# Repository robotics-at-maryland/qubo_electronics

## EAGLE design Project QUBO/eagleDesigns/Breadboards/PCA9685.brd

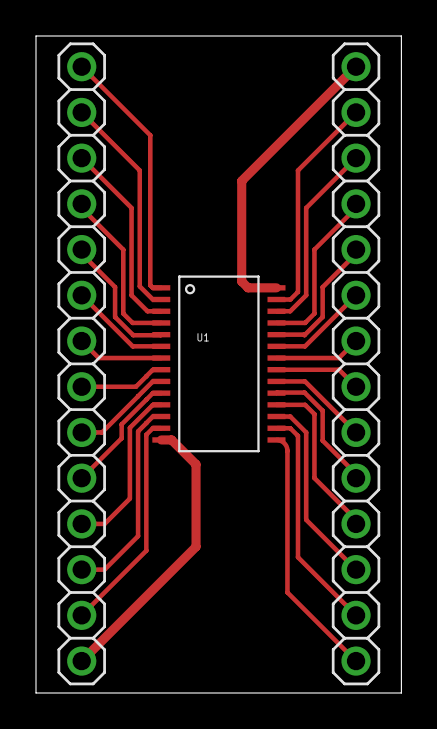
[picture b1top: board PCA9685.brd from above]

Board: 2 copper layers, 20.3 x 36.5 mm, 3 parts (0 on the bottom side), 28 nets.

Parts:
JP1, JP2: 1X14_ROUND
U1: PCA9685; TSSOP-28_4MM

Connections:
unnamed: JP1.1, U1.1
unnamed: JP1.2, U1.2
unnamed: JP1.3, U1.3
unnamed: JP1.4, U1.4
unnamed: JP1.5, U1.5
unnamed: JP1.6, U1.6
unnamed: JP1.7, U1.7
unnamed: JP1.8, U1.8
unnamed: JP1.9, U1.9
unnamed: JP1.10, U1.10
unnamed: JP1.11, U1.11
unnamed: JP1.12, U1.12
unnamed: JP1.13, U1.13
unnamed: JP1.14, U1.14
unnamed: JP2.1, U1.28
unnamed: JP2.2, U1.27
unnamed: JP2.3, U1.26
unnamed: JP2.4, U1.25
unnamed: JP2.5, U1.24
unnamed: JP2.6, U1.23
unnamed: JP2.7, U1.22
unnamed: JP2.8, U1.21
unnamed: JP2.9, U1.20
unnamed: JP2.10, U1.19
unnamed: JP2.11, U1.18
unnamed: JP2.12, U1.17
unnamed: JP2.13, U1.16
unnamed: JP2.14, U1.15

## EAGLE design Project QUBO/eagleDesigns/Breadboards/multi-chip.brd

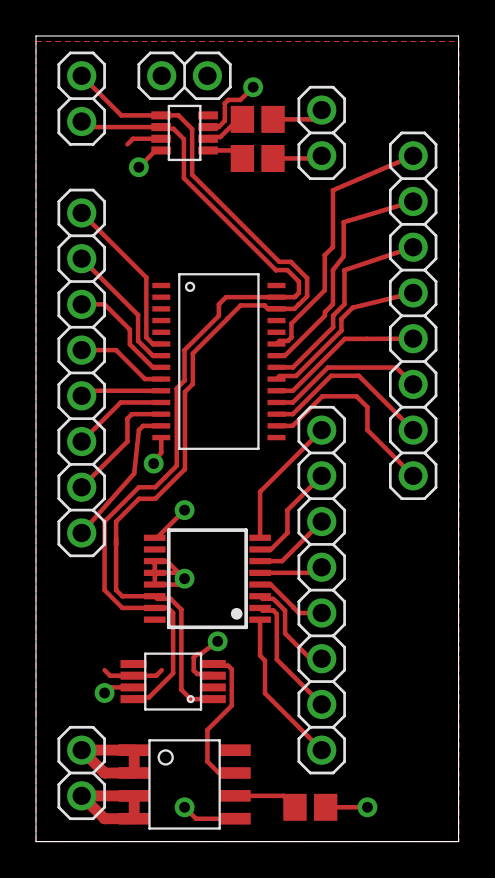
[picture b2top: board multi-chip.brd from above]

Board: 2 copper layers, 23.5 x 44.8 mm, 15 parts (0 on the bottom side), 36 nets.

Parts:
C1: 47n; C0805
I2C: 1X02
JP3, JP4: 1X02
JP5, JP8, JP9: 1X08
POWER: 1X02
R1, R2: 10; R0805
U1: PCA9685; TSSOP-28_4MM
U$1: ACS713SOIC; ACS713-SOIC
U$2: ADC121C021; VSSOP-8
U$3: ADS7828; TSSOP16
U$4: INA219SOT23; SOT-23-8

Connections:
5V: POWER.1, U1.1, U1.2, U1.3, U1.4, U1.5, U1.24, U1.28, U$1.P$8, U$2.P$5, U$2.P$6, U$3.10, U$3.16, U$4.P$4, U$4.P$7
GND: C1.2, POWER.2, U1.14, U$1.P$5, U$2.P$3, U$2.P$7, U$3.9, U$3.11, U$3.12, U$3.13, U$4.P$3, U$4.P$8
IN+: JP3.1, R1.1
IN-: JP3.2, R2.1
unnamed: C1.1, U$1.P$6
unnamed: R1.2, U$4.P$1
unnamed: R2.2, U$4.P$2
unnamed: JP4.1, U$1.P$1, U$1.P$2
unnamed: JP4.2, U$1.P$3, U$1.P$4
unnamed: U$1.P$7, U$2.P$4
unnamed: JP5.1, U$3.1
unnamed: JP5.2, U$3.2
unnamed: JP5.3, U$3.3
unnamed: JP5.4, U$3.4
unnamed: JP5.5, U$3.5
unnamed: JP5.6, U$3.6
unnamed: JP5.7, U$3.7
unnamed: JP5.8, U$3.8
unnamed: JP8.1, U1.6
unnamed: JP8.2, U1.7
unnamed: JP8.3, U1.8
unnamed: JP8.4, U1.9
unnamed: JP8.5, U1.10
unnamed: JP8.6, U1.11
unnamed: JP8.7, U1.12
unnamed: JP8.8, U1.13
unnamed: JP9.1, U1.23
unnamed: JP9.2, U1.22
unnamed: JP9.3, U1.21
unnamed: JP9.4, U1.20
unnamed: JP9.5, U1.19
unnamed: JP9.6, U1.18
unnamed: JP9.7, U1.17
unnamed: JP9.8, U1.16
SCL: I2C.2, U1.26, U$2.P$1, U$3.14, U$4.P$5
SDA: I2C.1, U1.27, U$2.P$8, U$3.15, U$4.P$6

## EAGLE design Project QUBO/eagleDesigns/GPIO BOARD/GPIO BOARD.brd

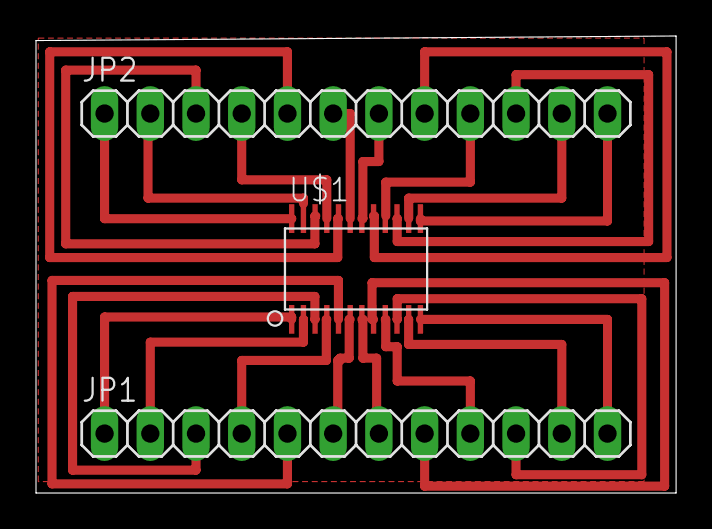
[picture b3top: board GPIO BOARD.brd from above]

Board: 2 copper layers, 35.6 x 25.4 mm, 3 parts (0 on the bottom side), 24 nets.

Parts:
JP1, JP2: 1X12
U$1: PCF8575C

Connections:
A0: JP2.4, U$1.21
A1: JP1.2, U$1.2
A2: JP1.3, U$1.3
GND: JP1.12, U$1.12
INT: JP1.1, U$1.1
P00: JP1.4, U$1.4
P01: JP1.5, U$1.5
P02: JP1.6, U$1.6
P03: JP1.7, U$1.7
P04: JP1.8, U$1.8
P05: JP1.9, U$1.9
P06: JP1.10, U$1.10
P07: JP1.11, U$1.11
P10: JP2.12, U$1.13
P11: JP2.11, U$1.14
P12: JP2.10, U$1.15
P13: JP2.9, U$1.16
P14: JP2.8, U$1.17
P15: JP2.7, U$1.18
P16: JP2.6, U$1.19
P17: JP2.5, U$1.20
SCL: JP2.3, U$1.22
SDA: JP2.2, U$1.23
VCC: JP2.1, U$1.24

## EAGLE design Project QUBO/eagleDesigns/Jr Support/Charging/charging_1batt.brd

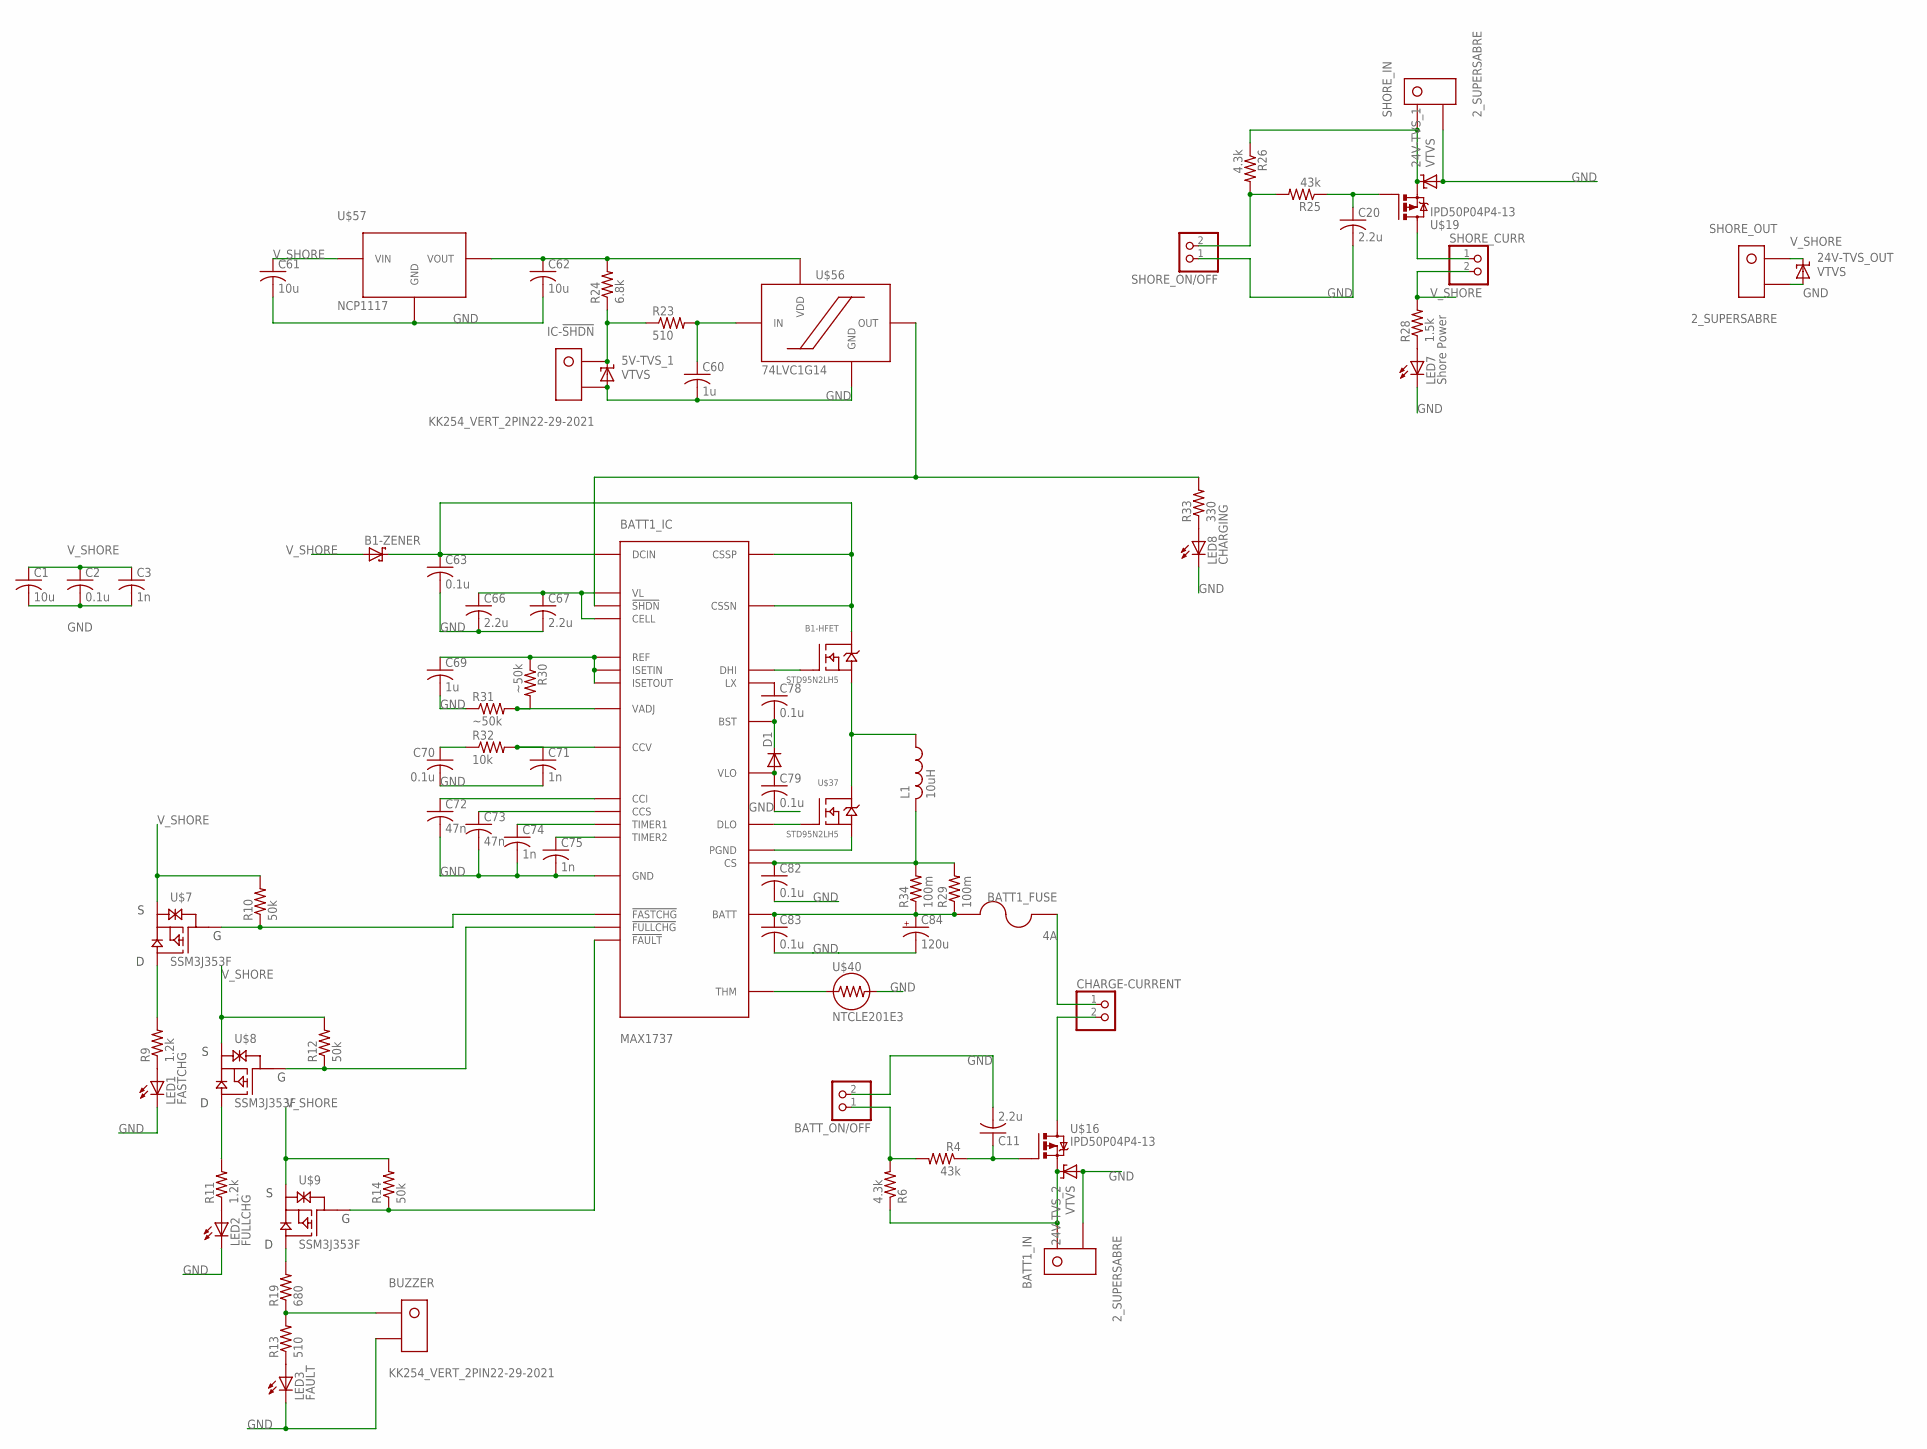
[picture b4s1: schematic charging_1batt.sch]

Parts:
5V-TVS_1, 24V-TVS_1, 24V-TVS_2, 24V-TVS_OUT: VTVS; DO-219AB
B1-HFET: STD95N2LH5; DPAK
B1-ZENER: SCHOTTKY-DIODESOD-106; SOD106-R
BATT1_FUSE: 4A; 154-OMNI-BLOK
BATT1_IC: MAX1737; QSOP28
BATT1_IN: 2_SUPERSABRE; SUPERSABRE_2CIRCUIT
BATT_ON/OFF: PINHD-1X2; 1X02
BUZZER: KK254_VERT_2PIN22-29-2021; KK254_VERT_2PIN
C1, C61, C62: 10u; C0805
C2, C63, C70, C78, C79, C82, C83: 0.1u; C0805
C3, C71, C74, C75: 1n; C0805
C11, C20, C66, C67: 2.2u; C0805
C60, C69: 1u; C0805
C72, C73: 47n; C0805
C84: 120u; E3,5-8
CHARGE-CURRENT: PINHD-1X2; 1X02
D1: DIODE-SOD123; SOD123
IC-!SHDN!: KK254_VERT_2PIN22-29-2021; KK254_VERT_2PIN
L1: 10uH; L6100
LED1: FASTCHG; CHIP-LED0805
LED2: FULLCHG; CHIP-LED0805
LED3: FAULT; CHIP-LED0805
LED7: Shore Power; CHIP-LED0805
LED8: CHARGING; CHIP-LED0805
R4, R25: 43k; R0805
R6, R26: 4.3k; R0805
R9, R11: 1.2k; R0805
R10, R12, R14: 50k; R0805
R13, R23: 510; R0805
R19: 680; R0805
R24: 6.8k; R0805
R28: 1.5k; R0805
R29, R34: 100m; R2512
R30, R31: ~50k; R0805
R32: 10k; R0805
R33: 330; R0805
SHORE_CURR: PINHD-1X2; 1X02
SHORE_IN: 2_SUPERSABRE; SUPERSABRE_2CIRCUIT
SHORE_ON/OFF: PINHD-1X2; 1X02
SHORE_OUT: 2_SUPERSABRE; SUPERSABRE_2CIRCUIT
U$7, U$8, U$9: SSM3J353F; SOT-346-3/S-MINI
U$16, U$19: IPD50P04P4-13; TO252-3
U$37: STD95N2LH5; DPAK
U$40: NTCLE201E3; 2-0.3MM-LEADS
U$56: 74LVC1G14; TSSOP5
U$57: NCP1117; SOT-223

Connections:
!SHDN!: BATT1_IC.18 (!SHDN!), R33.2, U$56.P$4 (OUT)
BATT1_P: 24V-TVS_2.P$2 (C), BATT1_IN.P$1, R6.1, U$16.TAB (D)
BATT_1: BATT1_FUSE.P$2, BATT1_IC.7 (BATT), C83.1, C84.+, R29.1, R34.1
CS_1: BATT1_IC.19 (CS), C82.1, L1.P$2 (2), R29.2, R34.2
FET-G_1: C11.1, R4.1, U$16.1 (G)
GND: 5V-TVS_1.P$1 (A), 24V-TVS_1.P$1 (A), 24V-TVS_2.P$1 (A), 24V-TVS_OUT.P$1 (A), BATT1_IC.6 (GND), BATT1_IN.P$2, BATT_ON/OFF.2, BUZZER.P$2, C1.2, C2.2, C3.2, C11.2, C20.2, C60.2, C61.2, C62.2, C63.2, C66.2, C67.2, C69.2, C70.2, C71.2, C72.2, C73.2, C74.2, C75.2, C79.2, C82.2, C83.2, C84.-, IC-!SHDN!.P$2, LED1.C, LED2.C, LED3.C, LED7.C, LED8.C, R31.1, SHORE_IN.P$2, SHORE_ON/OFF.1, SHORE_OUT.P$2, U$40.P$2 (2), U$56.P$3 (GND), U$57.P$1 (GND)
unnamed: CHARGE-CURRENT.2, U$16.3 (S)
unnamed: LED1.A, R9.1
unnamed: BATT1_FUSE.P$1, CHARGE-CURRENT.1
unnamed: SHORE_CURR.1, U$19.3 (S)
unnamed: LED3.A, R13.1
unnamed: LED2.A, R11.1
unnamed: R9.2, U$7.P$2 (D)
unnamed: BATT1_IC.16 (!FASTCHG!), R10.1, U$7.P$1 (G)
unnamed: R11.2, U$8.P$2 (D)
unnamed: BATT1_IC.17 (!FULLCHG!), R12.1, U$8.P$1 (G)
unnamed: BUZZER.P$1, R13.2, R19.1
unnamed: R19.2, U$9.P$2 (D)
unnamed: BATT1_IC.15 (!FAULT!), R14.1, U$9.P$1 (G)
unnamed: LED7.A, R28.1
unnamed: B1-HFET.TAB (D), B1-ZENER.C, BATT1_IC.26 (CSSN), BATT1_IC.27 (CSSP), BATT1_IC.28 (DCIN), C63.1
unnamed: C20.1, R25.1, U$19.1 (G)
unnamed: C60.1, R23.2, U$56.P$2 (IN)
unnamed: 5V-TVS_1.P$2 (C), IC-!SHDN!.P$1, R23.1, R24.1
unnamed: R25.2, R26.2, SHORE_ON/OFF.2
unnamed: BATT_ON/OFF.1, R4.2, R6.2
unnamed: C62.1, R24.2, U$56.P$5 (VDD), U$57.P$2 (VOUT), U$57.P$4 (VOUT)
unnamed: LED8.A, R33.1
unnamed: BATT1_IC.8 (VADJ), R30.2, R31.2
unnamed: C70.1, R32.1
unnamed: BATT1_IC.1 (VL), BATT1_IC.12 (CELL), C66.1, C67.1
unnamed: BATT1_IC.9 (CCV), C71.1, R32.2
unnamed: BATT1_IC.2 (ISETIN), BATT1_IC.3 (ISETOUT), BATT1_IC.5 (REF), C69.1, R30.1
unnamed: BATT1_IC.11 (CCI), C72.1
unnamed: BATT1_IC.10 (CCS), C73.1
unnamed: BATT1_IC.13 (TIMER1), C74.1
unnamed: BATT1_IC.14 (TIMER2), C75.1
unnamed: BATT1_IC.24 (LX), C78.1
unnamed: BATT1_IC.23 (BST), C78.2, D1.C
unnamed: BATT1_IC.21 (DLO), U$37.1 (G)
unnamed: B1-HFET.1 (G), BATT1_IC.25 (DHI)
unnamed: B1-HFET.3 (S), L1.P$1 (1), U$37.TAB (D)
unnamed: BATT1_IC.20 (PGND), U$37.3 (S)
unnamed: BATT1_IC.22 (VLO), C79.1, D1.A
unnamed: BATT1_IC.4 (THM), U$40.P$1 (1)
VIN: 24V-TVS_1.P$2 (C), R26.1, SHORE_IN.P$1, U$19.TAB (D)
V_SHORE: 24V-TVS_OUT.P$2 (C), B1-ZENER.A, C1.1, C2.1, C3.1, C61.1, R10.2, R12.2, R14.2, R28.2, SHORE_CURR.2, SHORE_OUT.P$1, U$7.P$3 (S), U$8.P$3 (S), U$9.P$3 (S), U$57.P$3 (VIN)

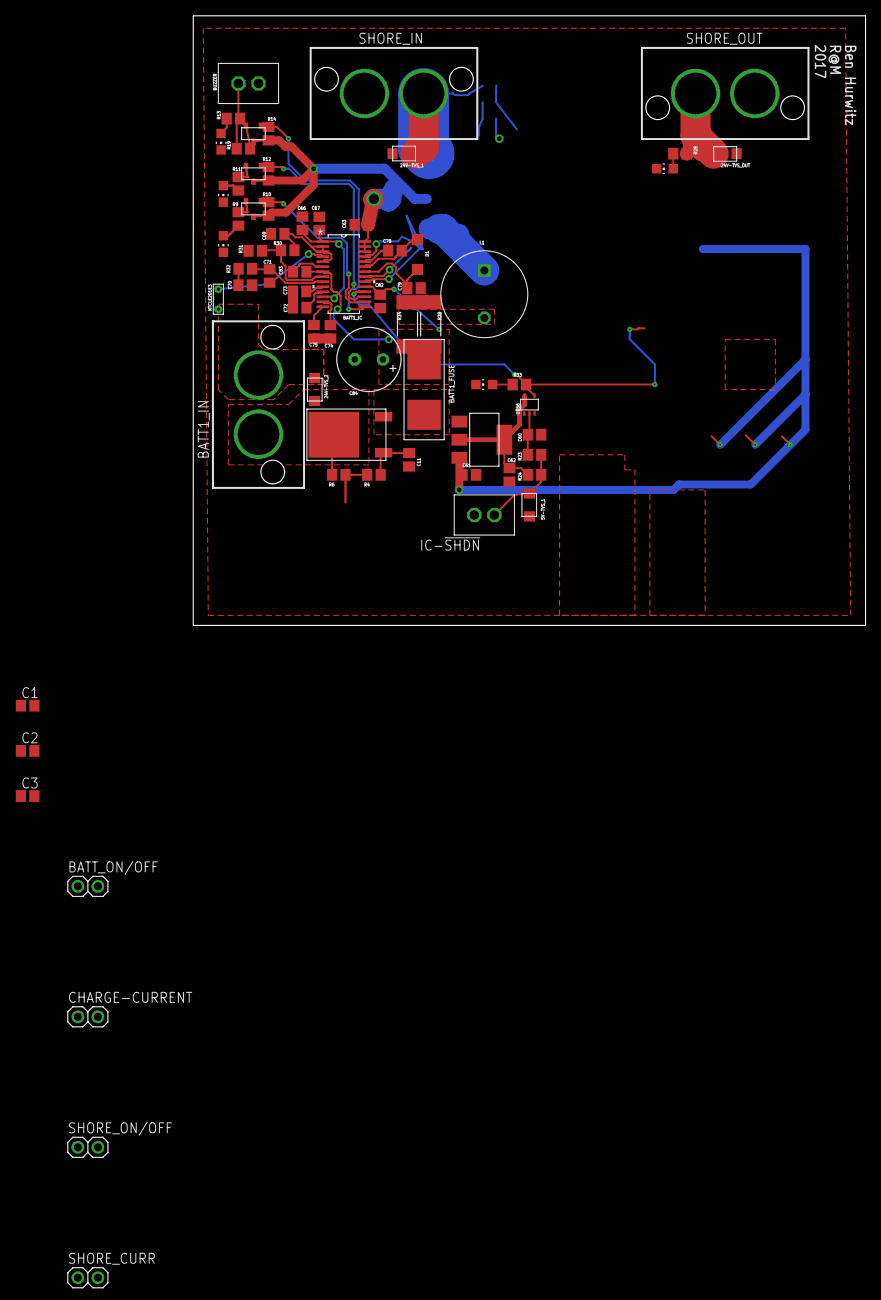
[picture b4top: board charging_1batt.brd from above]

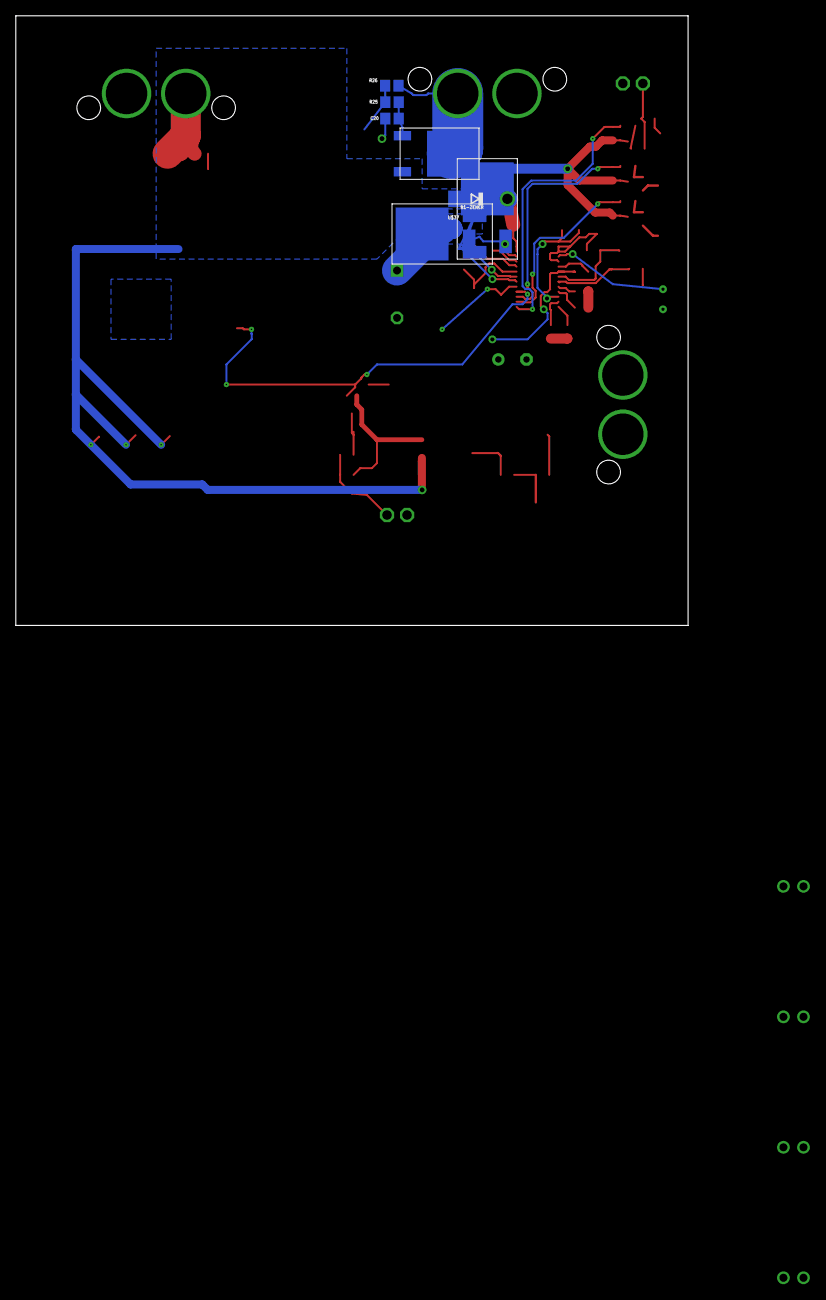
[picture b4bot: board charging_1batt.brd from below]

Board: 2 copper layers, 85.1 x 77.1 mm, 76 parts (7 on the bottom side), 47 nets.

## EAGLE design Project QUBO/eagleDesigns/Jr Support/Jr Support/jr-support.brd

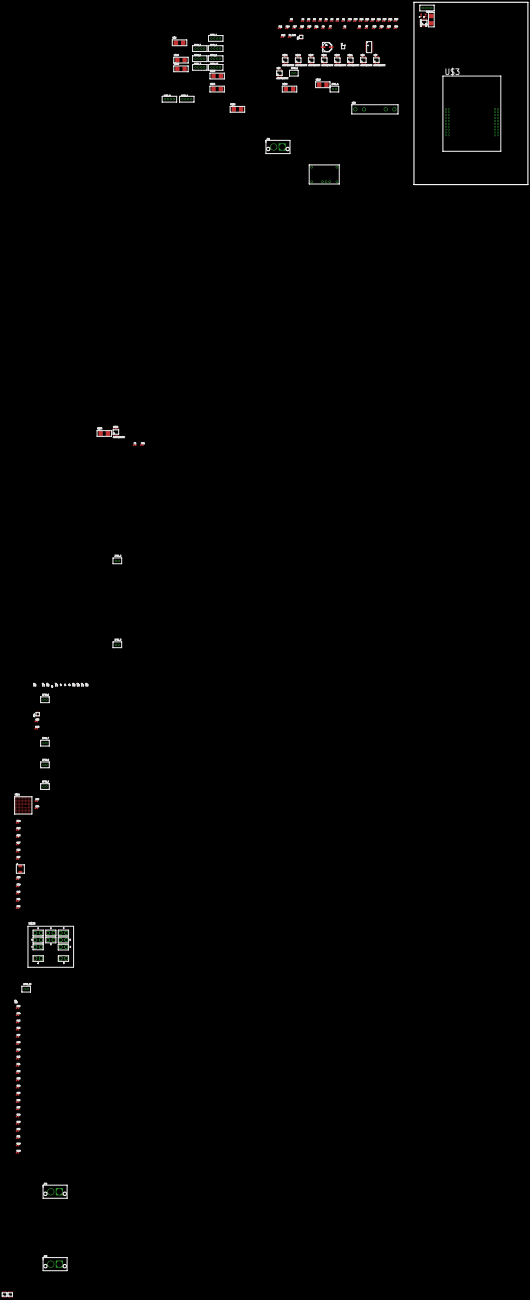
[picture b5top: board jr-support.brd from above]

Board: 4 copper layers, 144 parts (0 on the bottom side), 87 nets, no tracks yet.

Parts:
2PIN_1: Camera1 pwr; KK254_VERT_2PIN
2PIN_2: 12V reg switch; KK254_VERT_2PIN
2PIN_3: Relay switch; KK254_VERT_2PIN
2PIN_4: Ethernet switch pwr; KK254_VERT_2PIN
2PIN_6: UART; KK254_VERT_2PIN
2PIN_7: Vin_OUT; KK254_VERT_2PIN
2PIN_8: 12V_OUT; KK254_VERT_2PIN
2PIN_9: 5V_OUT; KK254_VERT_2PIN
2PIN_10: Camera2\ pwr; KK254_VERT_2PIN
4PIN_1, 4PIN_2, 4PIN_3, 4PIN_4, 4PIN_5, 4PIN_6, 4PIN_7, 4PIN_10: KK254_VERT_4PIN
4PIN_8: Depth Sensor; KK254_VERT_4PIN
4PIN_9: CPU PWR; KK254_VERT_4PIN
5V_REG: 21k; R0805
C1, C2, C5, C7, C9, C11, C13, C15, C17, C19, C21, C36: 0.1u; C0805
C3, C6, C8, C10, C12, C14, C16, C18, C20, C22, C31: 47n; C0805
C4: 100u; PANASONIC_F
C23, C33: 100p; C0805
C24, C25, C26: 100n; C0805
C32, C34, C43, C44, C45, C46, C47, C48, C49, C50, C51, C52, C53, C54, C55, C56, C57, C58, C59, C60, C61: C0805
C37: 100u; C0805
C38, C39: 10u; C0805
C40, C41: 2.2u; C0805
C42: 1u; C0805
JP1, JP2, JP3: SUPERSABRE_2CIRCUIT
L1: 3.3u; HCMA0703
R1, R2, R3, R4, R5, R6, R9, R10, R11, R18, R19: 10k; R0805
R7, R8: 4.7k; R0805
R12, R13: 200k; R0805
R14: 1.5k; R0805
R15: 1k; R0805
R16: 7.15k; R0805
R17: 8m; R0805
U1: PCA9685; TSSOP-28_4MM
U2: BME280; BME280_LGA
U$1: PTN78060W
U$2, U$4, U$7, U$9, U$11, U$13, U$15, U$17, U$19, U$22, U$35: ACS713SOIC; ACS713-SOIC
U$3: TIVA-C_EVAL
U$5: 25A Fuse; 1.25"_FUSECLIPS
U$6, U$8, U$10, U$12, U$14, U$16, U$18, U$20, U$23, U$36: 4A Fuse; 154-OMNI-BLOK
U$21, U$59: SM8
U$24: LTM4605; LGA-141
U$25: KUHP-5XX1-XX; KUHP_6.35MM-QUICK-CONNECT
U$26, U$47, U$48, U$49, U$53: 12V; SOD-323
U$27, U$28: LTC4364MSOP; MSOP16
U$46: 5V; SOD-323
U$50, U$52, U$54: 5V; SOD-923
U$51: 3V3; SOD-923
U$55, U$56, U$58: 24V; SOD-323

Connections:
3V3: C24.1, C25.1, C26.1, C52.1, R10.2, R11.2, U2.P$2, U2.P$6, U2.P$8, U$3.1-1, U$21.P$2, U$51.P$2, U$59.P$2
5V: 2PIN_2.P$1, 2PIN_4.P$1, 2PIN_9.P$1, 4PIN_8.P$4, C1.1, C2.1, C5.1, C7.1, C9.1, C11.1, C13.1, C15.1, C17.1, C19.1, C21.1, C43.1, C48.1, C51.1, C53.1, R1.2, R2.2, R3.2, R4.2, R5.2, R6.2, R7.2, R8.2, R9.2, R12.2, R13.2, U1.28, U$2.P$8, U$3.3-1, U$4.P$8, U$7.P$8, U$9.P$8, U$11.P$8, U$13.P$8, U$15.P$8, U$17.P$8, U$19.P$8, U$20.P$2, U$22.P$8, U$35.P$8, U$46.P$2, U$50.P$2, U$52.P$2
12V: 2PIN_8.P$1, 4PIN_9.P$3, 4PIN_9.P$4, C44.1, C50.1, U$36.P$2, U$48.P$2, U$49.P$2
AIN0: U$3.3-9, U$19.P$7
AIN1: U$2.P$7, U$3.3-8, U$35.P$7
AIN2: U$3.3-7, U$4.P$7
AIN3: U$3.2-3, U$7.P$7
AIN4: U$3.3-6, U$9.P$7
AIN5: U$3.3-5, U$11.P$7
AIN8: U$3.1-6, U$13.P$7
AIN9: U$3.1-5, U$15.P$7
AIN10: U$3.1-7, U$17.P$7
AIN11: U$3.1-2, U$22.P$7
CPU_ON: 2PIN_2.P$2, C34.1, U$24.A8, U$55.P$2
GND: 2PIN_1.P$2, 2PIN_4.P$2, 2PIN_7.P$2, 2PIN_8.P$2, 2PIN_9.P$2, 2PIN_10.P$2, 4PIN_1.P$1, 4PIN_1.P$3, 4PIN_2.P$1, 4PIN_2.P$3, 4PIN_3.P$1, 4PIN_3.P$3, 4PIN_4.P$1, 4PIN_4.P$3, 4PIN_5.P$1, 4PIN_5.P$3, 4PIN_6.P$1, 4PIN_6.P$3, 4PIN_7.P$1, 4PIN_7.P$3, 4PIN_8.P$3, 4PIN_9.P$1, 4PIN_9.P$2, 4PIN_10.P$1, 4PIN_10.P$3, 5V_REG.2, C1.2, C2.2, C3.2, C4.-, C5.2, C6.2, C7.2, C8.2, C9.2, C10.2, C11.2, C12.2, C13.2, C14.2, C15.2, C16.2, C17.2, C18.2, C19.2, C20.2, C21.2, C22.2, C23.2, C24.2, C25.2, C26.2, C31.2, C32.2, C33.2, C34.2, C36.2, C37.2, C38.2, C39.2, C40.2, C41.2, C42.2, C43.2, C44.2, C46.2, C47.2, C48.2, C49.2, C50.2, C51.2, C52.2, C53.2, C54.2, C55.2, C56.2, C57.2, C58.2, C59.2, C60.2, C61.2, JP1.P$1, JP2.P$1, JP3.P$1, R15.1, R16.1, R17.1, R18.1, R19.2, U1.14, U1.23, U1.25, U2.P$1, U2.P$5, U2.P$7, U$1.P$1, U$1.P$2, U$2.P$5, U$3.2-1, U$3.3-2, U$4.P$5, U$7.P$5, U$9.P$5, U$11.P$5, U$13.P$5, U$15.P$5, U$17.P$5, U$19.P$5, U$21.P$1, U$22.P$5, U$24.A1, U$24.A2, U$24.A3, U$24.A5, U$24.A7, U$24.A9, U$24.A11, U$24.A12, U$24.B1, U$24.B2, U$24.B3, U$24.B4, U$24.B10, U$24.B11, U$24.B12, U$24.C1, U$24.C2, U$24.C3, U$24.C4, U$24.C5, U$24.C6, U$24.C7, U$24.C8, U$24.C9, U$24.C10, U$24.C11, U$24.C12, U$24.D1, U$24.D2, U$24.D3, U$24.D4, U$24.D5, U$24.D6, U$24.D7, U$24.D8, U$24.D9, U$24.D10, U$24.D11, U$24.D12, U$24.E3, U$24.E4, U$24.E5, U$24.E6, U$24.E7, U$24.E8, U$24.E9, U$24.E10, U$24.E11, U$24.E12, U$26.P$1, U$35.P$5, U$46.P$1, U$47.P$1, U$48.P$1, U$49.P$1, U$50.P$1, U$51.P$1, U$52.P$1, U$53.P$1, U$54.P$1, U$55.P$1, U$56.P$1, U$58.P$1, U$59.P$1
unnamed: 5V_REG.1, U$1.P$6
unnamed: R1.1, U$3.2-5
unnamed: R6.1, U1.5
unnamed: R5.1, U1.4
unnamed: R4.1, U1.3
unnamed: R3.1, U1.2
unnamed: C4.+, C40.1, U$2.P$1, U$2.P$2, U$54.P$2
unnamed: R2.1, U1.1
unnamed: R9.1, U1.24
unnamed: C3.1, U$2.P$6
unnamed: C8.1, U$7.P$6
unnamed: C6.1, U$4.P$6
unnamed: 4PIN_1.P$4, C54.1, U$6.P$2
unnamed: U$4.P$3, U$4.P$4, U$6.P$1
unnamed: 4PIN_2.P$4, C55.1, U$8.P$2
unnamed: U$7.P$3, U$7.P$4, U$8.P$1
unnamed: C10.1, U$9.P$6
unnamed: 4PIN_3.P$4, C57.1, U$10.P$2
unnamed: U$9.P$3, U$9.P$4, U$10.P$1
unnamed: C12.1, U$11.P$6
unnamed: 4PIN_4.P$4, C56.1, U$12.P$2
unnamed: U$11.P$3, U$11.P$4, U$12.P$1
unnamed: C14.1, U$13.P$6
unnamed: 4PIN_5.P$4, C58.1, U$14.P$2
unnamed: U$13.P$3, U$13.P$4, U$14.P$1
unnamed: C16.1, U$15.P$6
unnamed: 4PIN_6.P$4, C59.1, U$16.P$2
unnamed: U$15.P$3, U$15.P$4, U$16.P$1
unnamed: C18.1, U$17.P$6
unnamed: 4PIN_7.P$4, C61.1, U$18.P$2
unnamed: L1.P$1, U$24.J1, U$24.J2, U$24.J3, U$24.J4, U$24.K1, U$24.K2, U$24.K3, U$24.K4, U$24.L1, U$24.L2, U$24.L3, U$24.L4, U$24.M1, U$24.M2, U$24.M3, U$24.M4
unnamed: C20.1, U$19.P$6
unnamed: U$5.P$1, U$5.P$2, U$19.P$3, U$19.P$4
unnamed: R19.1, U$25.AA, U$25.AB
unnamed: C22.1, U$22.P$6
unnamed: 4PIN_10.P$4, C60.1, U$23.P$2
unnamed: R14.2, U$24.F5
unnamed: C23.1, R12.1, U$21.P$7, U$21.P$8
unnamed: R14.1, R15.2, U$24.B8
unnamed: R16.2, U$24.B6
unnamed: R17.2, U$24.A4, U$24.F10, U$24.F11, U$24.F12, U$24.G5, U$24.G6, U$24.G7, U$24.G8, U$24.G9, U$24.G10, U$24.G11, U$24.G12, U$24.H5, U$24.H6, U$24.H7, U$24.H8, U$24.H9, U$24.H10, U$24.H11, U$24.H12, U$24.J5, U$24.J6, U$24.J7, U$24.K5, U$24.K6, U$24.L5, U$24.L6, U$24.M5, U$24.M6
unnamed: C36.1, U$24.A6
unnamed: L1.P$2, U$24.J8, U$24.J9, U$24.K7, U$24.K8, U$24.K9, U$24.L7, U$24.L8, U$24.L9, U$24.M7, U$24.M8, U$24.M9
unnamed: U$22.P$3, U$22.P$4, U$23.P$1
unnamed: U$17.P$3, U$17.P$4, U$18.P$1
unnamed: C31.1, U$35.P$6
unnamed: U$2.P$3, U$2.P$4, U$20.P$1
unnamed: U$35.P$3, U$35.P$4, U$36.P$1
unnamed: C37.1, U$24.E1, U$24.E2, U$24.F1, U$24.F2, U$24.F3, U$24.F4, U$24.G1, U$24.G2, U$24.G3, U$24.G4, U$24.H1, U$24.H2, U$24.H3, U$24.H4, U$35.P$1, U$35.P$2, U$53.P$2
unnamed: C33.1, R13.1, U$59.P$7, U$59.P$8
RELAY-BATT: U$25.5A, U$25.5B
RELAY-CTRL: U$25.BA, U$25.BB
RELAY-SHORE: U$25.2A, U$25.2B
RELAY_CTRL: 2PIN_3.P$2, C32.1, R18.2, U$56.P$2
RELAY_OUT: C38.1, C39.1, C41.1, C42.1, U$1.P$4, U$19.P$1, U$19.P$2, U$24.J10, U$24.J11, U$24.J12, U$24.K10, U$24.K11, U$24.K12, U$24.L10, U$24.L11, U$24.L12, U$24.M10, U$24.M11, U$24.M12, U$25.7A, U$25.7B, U$58.P$2
RX: U$3.1-3, U$59.P$6
RX-3V3: 2PIN_6.P$1, U$59.P$3
SCL1: R8.1, U1.26, U$3.1-9, U$21.P$6
SCL-3V3: 4PIN_8.P$1, R11.1, U2.P$4, U$21.P$3
SDA1: R7.1, U1.27, U$3.1-10, U$21.P$5
SDA-3V3: 4PIN_8.P$2, R10.1, U2.P$3, U$21.P$4
T1_PWM: 4PIN_1.P$2, U1.6
T2_PWM: 4PIN_2.P$2, U1.7
T3_PWM: 4PIN_3.P$2, U1.8
T4_PWM: 4PIN_4.P$2, U1.9
T5_PWM: 4PIN_5.P$2, U1.10
T6_PWM: 4PIN_6.P$2, U1.11
T7_PWM: 4PIN_7.P$2, U1.12
T8_PWM: 4PIN_10.P$2, U1.13
TX: U$3.1-4, U$59.P$5
TX-3V3: 2PIN_6.P$2, U$59.P$4
V_THRUST: 2PIN_1.P$1, 2PIN_7.P$1, 2PIN_10.P$1, C46.1, C47.1, C49.1, U$4.P$1, U$4.P$2, U$5.P$3, U$5.P$4, U$7.P$1, U$7.P$2, U$9.P$1, U$9.P$2, U$11.P$1, U$11.P$2, U$13.P$1, U$13.P$2, U$15.P$1, U$15.P$2, U$17.P$1, U$17.P$2, U$22.P$1, U$22.P$2, U$26.P$2, U$47.P$2
